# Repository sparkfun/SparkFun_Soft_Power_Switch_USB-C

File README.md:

SparkFun Soft Power Switch - USB-C
===================================================

[*SparkFun Soft Power Switch - USB-C (PRT-27081)*](https://www.sparkfun.com/products/27081)

The Soft Power Switch Mk2 is a passive, hard on/off switch with software feedback and control. In other words, it's like the on/off switch on a laptop. A simple press will turn the system on. Another press can (with MCU intervention) turn off the system. And if things go really wrong, pressing and holding the button for ~7 seconds will force a power-down. If you're building something with an enclosed Thing Plus board and need a good power button, this is the board you need.

The [Mk1 Soft Power Switch](https://www.sparkfun.com/products/17870) is great, but we do see occasional issues caused by component tolerances or the operating temperature. Mk2 is based on an application note by Texas Instruments, and is a completely digital design. It is based around a 74LVC1G175 D-type flip-flop - remember those?! - and is insensitive to temperature and component variation. It also includes improvements like: an over-current self-resetting 2A fuse; input and output LEDs. This version has USB-C connectors, but we also have a version with [JST 2mm](https://www.sparkfun.com/products/25365) battery connectors.

The PUSH pin can act as an output to a microcontroller indicating the state of the power button (high = not pressed, low = user is pressing power button). This can be used as an input to your firmware to begin to shut down before power is lost. PUSH is an open-drain output and requires a pull-up. Alternatively, the OFF pin can be driven **high** by the system forcing fast power off via software. (For Mk1, the Fast Off pin was driven **low**.)

The most common use case is something like this:

* Microcontroller begins running code and checks to see if the power button is still being pressed for X milliseconds.
* If not, it's just a tap, go back to sleep.
* If yes, power up and run normal program.

Later...

* User presses power button in normal program
* If power button is pressed for <X milliseconds, it's just a tap, ignore.
* If power button is pressed for >X milliseconds, it's time to power down.

The wake-up and power-down times can be tweaked for your own user experience but we found 500ms for power up and 2s for power down work really well.

If needed, pads are provided for a larger, external button.

The Soft Power Switch supports battery charging. If the target device has onboard LiPo charging, current can be passed back through the switch circuit and charge the battery.

<b>Heads up!</b> The Soft Power Switch - USB-C works up to 5.5V only. (Mk1 is good up to 12V.)

Pros:

* Very low µA quiescent current
* Hard override power down in case your microcontroller loses its mind
* PUSH and OFF pins can be connected to a microcontroller
* Supports battery charging
* USB data feed-through

Cons:

* Limited to 2A continuous, 4A peak (fuse protected)
* No AC loads

Features
-------------------
* Input voltage: 5V nominal (5.5V maximum, 1.8V minimum)
* Maximum current draw: 2A continuous, 4A peak (fuse protected)
* Very low µA quiescent current
* Hard override: push and hold the button for ~7 seconds
* 1" x 1" PCB
* USB data feed-through
* LEDs: VIN and VOUT (can be disabled if desired)
* Breakouts:
    * GND, VIN, VOUT
    * BTN: if desired, connect an external button between BTN and GND
    * PUSH: open-drain output, requires pull-up, low indicates button is pushed
    * OFF: drive high to turn the output off

Repository Contents
-------------------

* **.github/workflows** - YAML files used for GitHub Actions and GitHub Pages/mkdocs
* **/Examples** - Example sketches demonstrating how to read and control the switch
* **/Hardware** - KiCad design files (kicad_pro, .kicad_pcb, .kicad_sch)
  * **/Production** - Production panel files
* **/docs** - Online documentation files
  * **/assets** - Folder containing all the file assets used for product documentation
    *  **/3d_model** - Exported 3D models from KiCad
    * **/board_files** - Copy of design files used for product documentation
    * **/component_documentation** - Datasheets and manuals for hardware components
    * **/img** - Images for product documentation
  * **/github** - Files stating how to contribute and filing issues used for product documentation
  * **/javascript** - Folder containing custom javascript used for product documentation
  * **/stylesheet** - Folder containing CSS files used for product documentation
* **/overrides** - Customization files used for product documentation
  * **/.icons** - Icons used for GitHub used for product documentation
  * **./partials** - Used for product documentation
* **LICENSE.md** contains the license information

Documentation
--------------
* **[Hookup Guide](https://docs.sparkfun.com/SparkFun_Soft_Power_Switch_USB-C)** - Basic hookup guide for the Soft Power Switch - USB-C.

Product Versions
----------------
* [PRT-27081](https://www.sparkfun.com/products/27081) - SparkFun Red Release
* [SPX-25366](https://www.sparkfun.com/products/25366) - Original SparkX Release Mk2
* [SPX-17870](https://www.sparkfun.com/products/retired/17870) - Original SparkX Release Mk1

Version History
---------------
* v1.0 - SparkFun Soft Power Switch - USB-C (PRT-27081)
* v01 - SparkX Soft Power Switch Mk2 - USB-C (SPX-25366)
* v1.0 - SparkX Soft Power Switch Mk1 (JST 2mm) (SPX-17870)

License Information
-------------------

This product is _**open source**_!

Please review the LICENSE.md file for license information.

If you have any questions or concerns on licensing, please contact technical support on our [SparkFun forums](https://forum.sparkfun.com/viewforum.php?f=123).

Distributed as-is; no warranty is given.

- Your friends at SparkFun.

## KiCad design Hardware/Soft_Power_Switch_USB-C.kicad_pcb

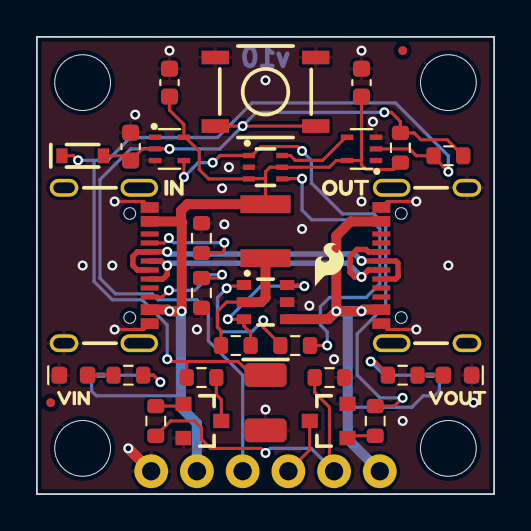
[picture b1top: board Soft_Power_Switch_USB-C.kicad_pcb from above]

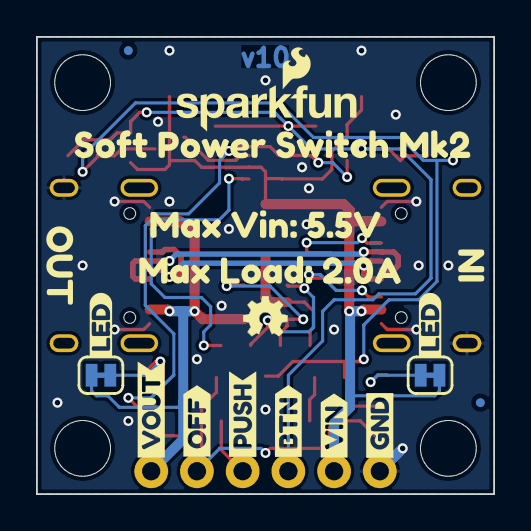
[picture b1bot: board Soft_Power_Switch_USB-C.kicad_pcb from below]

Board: 2 copper layers, 25.4 x 25.4 mm, 59 parts (18 on the bottom side), 24 nets.

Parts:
C1, C3: 1.0uF; C_0603_1608Metric
C2: 47uF; EIA-3528
C4: 0.1uF; C_0603_1608Metric
D1: BAS16J; SOD-323
D2, D3: Red; LED_0603_1608Metric_Red
F1: 6V/2.0A/4.0A; 1210
FID1, FID2, FID3, FID4: Fiducial_0.5mm; Fiducial_0.5mm_Mask1mm
G3: OSHW_Logo; Creative_Commons_License
J1, J2: USB_C_Receptacle; USB-C_16
J3: Conn_01x06; 1x06
JP1, JP2: Jumper_2_NC_Trace
Q1, Q2: BSS138; SOT23-3
Q3: SIL2308; SOT23-6-Tight
R1, R6, R8, R9: 1k; R_0603_1608Metric
R2: 200k; R_0603_1608Metric
R3, R4, R7: 10k; R_0603_1608Metric
R5: 100; R_0603_1608Metric
R10: 100k; R_0603_1608Metric
R11, R12: 5.1k; R_0603_1608Metric
Ref**: Val**; OSHW_Logo_2.5mm
ST1, ST2, ST3, ST4: Standoff
SW1: SMD_5.2x5.2mm_h2.5mm; Push_SMD_5.2x5.2mm_h2.5mm
U2: SN74LVC1G14DCK; SOT-353
U3: SN74LVC1G17DCK; SOT-353
U4: SN74LVC1G175DCK; SOT-323
kibuzzard-65F19FA6, kibuzzard-65F19FA6#2: G***; kibuzzard-65F19FA6
kibuzzard-65F053F1: G***; kibuzzard-65F053F1
kibuzzard-65F056B4: G***; kibuzzard-65F056B4
kibuzzard-65F056D8: G***; kibuzzard-65F056D8
kibuzzard-65F056F7: G***; kibuzzard-65F056F7
kibuzzard-65F174FD: G***; kibuzzard-65F174FD
kibuzzard-65F0543A: G***; kibuzzard-65F0543A
kibuzzard-65F0634B: G***; kibuzzard-65F0634B
kibuzzard-65F0636B: G***; kibuzzard-65F0636B
kibuzzard-65F1758C: G***; kibuzzard-65F1758C
kibuzzard-65F05416: G***; kibuzzard-65F05416
kibuzzard-65F05472: G***; kibuzzard-65F05472
kibuzzard-65F05495: G***; kibuzzard-65F05495
kibuzzard-65F05604: G***; kibuzzard-65F05604
kibuzzard-65F05628: G***; kibuzzard-65F05628
kibuzzard-65F05644: G***; kibuzzard-65F05644

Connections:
BTN: C1.1, D1.A, J3.4, R1.2, R2.2, SW1.2, U2.2
EN: R9.2, U4.4 (Q)
GND: C1.2, C2.2, C3.2, C4.2, D2.1 (K), D3.1 (K), J1.GND, J1.S (SHIELD), J2.GND, J2.S (SHIELD), J3.6, Q1.2 (S), Q2.2 (S), Q3.5 (S), R7.2, R11.2, R12.2, SW1.1, U2.3 (GND), U3.3 (GND), U4.2 (GND)
unnamed: C2.1, D1.C, R2.1, R5.1, U3.2
unnamed: D2.2 (A), R3.2
unnamed: D3.2 (A), R4.2
unnamed: J1.A5 (CC1), R12.1
unnamed: J1.B5 (CC2), R11.1
unnamed: J1.A6 (D+), J1.B6 (D+), J2.A6 (D+), J2.B6 (D+)
unnamed: J1.A7 (D-), J1.B7 (D-), J2.A7 (D-), J2.B7 (D-)
unnamed: JP1.1 (A), R3.1
unnamed: JP2.1 (A), R4.1
unnamed: Q1.3 (D), R5.2
unnamed: Q1.1 (G), R6.1
unnamed: Q2.1 (G), R8.2
unnamed: Q3.3 (G), Q3.6 (D), R10.1
unnamed: Q3.1 (G), R9.1
unnamed: F1.1, Q3.2 (1), R10.2
unnamed: R8.1, U2.4, U4.1 (CLK)
unnamed: U3.4, U4.6 (~CLR)
OFF: J3.2, R6.2, R7.1
PUSH: J3.3, Q2.3 (D)
VIN: C3.1, C4.1, F1.2, J1.VBUS, J3.5, JP1.2 (B), R1.1, U2.5 (VCC), U3.5 (VCC), U4.3 (D), U4.5 (VCC)
VOUT: J2.VBUS, J3.1, JP2.2 (B), Q3.4 (D)

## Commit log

2024-11-01 Initial GitHub Pages Push
2024-11-01 Update Product Name
2024-11-08 Update Tutorial
2024-11-15 Add Hardware Overview and Hookup
2024-11-15 Fix typo
2024-11-20 Fix links to files
2024-11-21 Adjust product name and formatting
2024-11-21 Fix broken links
2024-11-21 Deployed 6079ee3 with MkDocs version: 1.6.1
2025-09-11 Remove git-authors
2026-06-03 Deployed 488c64f with MkDocs version: 1.6.1

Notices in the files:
parts and their libraries:
https://creativecommons.org/licenses/by-sa/4.0
Released under the Creative Commons Attribution Share-Alike 4.0 License
